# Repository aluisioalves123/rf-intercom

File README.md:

# RF Intercom

Interfone de apertar para falar, **sem fio**: as duas unidades conversam por rádio (nRF24L01+ com antena) e só precisam de uma tomada. Na prática é um walkie talkie de mesa, ligado na energia em vez de bateria, e por isso o nome interfone.

Projeto completo feito em casa: circuito, placa de circuito impresso fresada numa CNC caseira, firmware de áudio digital e caixa impressa em 3D.

**As duas unidades conversando** (com som):

https://github.com/user-attachments/assets/871d9580-77c3-4d14-9feb-cfa74ef9aef5

## Como funciona

1. Ao apertar o botão, a unidade toca um bipe curto e passa a transmitir.
2. O microfone de eletreto passa por um pré-amplificador com um transistor BC547 e chega na entrada analógica do Arduino.
3. O Arduino amostra a voz a 8 kHz, com 8 bits, junta 32 amostras em cada pacote e envia pelo nRF24 a 250 kbps.
4. A outra unidade guarda os pacotes numa fila circular e os toca no ritmo certo, por interrupção de timer, gerando o áudio por PWM.
5. O sinal passa pelo potenciômetro de volume e pelo amplificador PAM8403 até o alto-falante.

Ao soltar o botão, a unidade volta a escutar. O mesmo firmware roda nas duas unidades.

## Hardware

| Bloco | Componentes |
|---|---|
| MCU | Arduino Nano ou LGT8F328P (mesma pinagem) |
| Rádio | Módulo nRF24L01+ PA/LNA com antena SMA, desacoplado com 100 µF + 100 nF |
| Microfone | Cápsula de eletreto + pré-amplificador com BC547, alimentação filtrada por RC |
| Saída de áudio | PWM no D9, resistor de 33k, potenciômetro de 5k e módulo PAM8403 |
| Alto-falante | 8 Ω, 40 mm |
| Alimentação | 5 V pelo USB do Arduino; 3,3 V do próprio Arduino para o rádio |

O esquemático e a placa estão em [`hardware/`](hardware/) (KiCad).

## Placa

A placa tem 85 × 52 mm, face simples, com solda só no lado de baixo. Ela foi pensada desde o início para ser fresada em casa: ilhas grandes, trilhas de 1 mm, isolação de 0,5 mm, áreas livres nos cantos para as garras e dois fiduciais para alinhar a placa virada.

O **posicionamento e o roteamento** foram feitos por um plugin de KiCad que eu desenvolvi para posicionamento e roteamento automáticos. A fabricação usou os meus plugins para a fresa, que geram o G-code direto do KiCad, com voos de teste antes de cortar e medição da altura da placa:

- Plugin de posicionamento e roteamento para KiCad: [kicad-cnc-router](https://github.com/aluisioalves123/kicad-cnc-router)
- Plugins da fresa (exportação do KiCad e Candle): [fresa-pcb](https://github.com/aluisioalves123/fresa-pcb)

Os arquivos de fabricação estão em [`hardware/fabrication/`](hardware/fabrication/): gerbers, G-code das três fases (cobre de cima, furação, cobre de baixo) e o passo a passo de montagem com uma imagem por etapa.

Saindo da fresa, debaixo do pó de fenolite:

Placa fresada, vista contra a luz:

## Firmware

Em [`firmware/`](firmware/), para a Arduino IDE com a biblioteca [RF24](https://github.com/nRF24/RF24):

| Sketch | Para que serve |
|---|---|
| `intercom` | Firmware das duas unidades |
| `intercom_debug` | Igual ao `intercom`, mais um contador de pacotes por segundo no Monitor Serial (usado para diagnosticar o rádio) |
| `mic_test` | Mostra o sinal do microfone no Plotter Serial, para testar o pré-amplificador |

Pontos principais:

- **Áudio a 8 kHz:** a captura é cronometrada por `micros()`, e a reprodução usa uma interrupção do Timer2 a 8 kHz.
- **Fila circular de 256 amostras**, com índices de 8 bits que dão a volta sozinhos. A reprodução só começa com 96 amostras guardadas, para absorver a irregularidade do rádio.
- **PWM rápido de 8 bits no Timer1** para o áudio. Quando não está tocando, o pino fica solto, para não gerar chiado.
- **Remoção do nível DC do microfone** por média móvel, com ganho ajustável.
- **Rádio sem confirmação de recebimento:** em áudio ao vivo, reenviar um pacote atrasado é pior do que perdê-lo.
- **Funciona nos dois microcontroladores:** o Timer2 se ajusta ao clock (16 MHz no Nano, 32 MHz no LGT).

## Caixa

Em [`mechanical/`](mechanical/): modelada em OpenSCAD a partir das medidas reais da placa montada e impressa em PETG.

- A placa fica virada dentro da caixa, com o rádio, o botão e o amplificador voltados para a tampa.
- Saída retangular para o USB e rasgo para a antena, fechado por uma lingueta da tampa.
- Alto-falante preso por três presilhas de encaixe. Knob próprio para o potenciômetro.
- Tampa presa por parafusos M3 autoatarraxantes, deitados nas paredes compridas.

Os STLs prontos estão em [`mechanical/stl/`](mechanical/stl/), e o [`assembly.scad`](mechanical/assembly.scad) mostra a placa dentro da caixa.

As imagens do modelo são de uma versão anterior da caixa: grade do alto-falante com furos redondos e pinos compridos na tampa, que foram retirados. A versão atual usa rasgos na grade, como na unidade da esquerda na foto do topo.

## O que deu errado e como foi resolvido

**Mau contato na própria protoboard.** Um bloco falhava, mas o componente funcionava em outro lugar da protoboard, então o problema não era ele. Embaixo da protoboard havia protuberâncias no plástico. Abrindo, as barras metálicas estavam quase saindo dos encaixes. Recoloquei as barras e reforcei com fita isolante, e a partir daí o nRF24 passou a funcionar.

**PAM8403 oscilando.** A alimentação do amplificador era compartilhada com os outros módulos da montagem. Um fio dedicado, direto da alimentação do Arduino até o PAM8403, sem passar por outros componentes, resolveu.

**Ruído da alimentação USB.** Ligado no USB de um computador, aparece um ruído no áudio. Filtros RC em vários pontos do circuito (inclusive nas alimentações do microfone e do pré-amplificador) reduziram bastante, mas não eliminaram. Num carregador de tomada ou numa fonte de bancada, ele desaparece.

**Curto entre 5 V e GND na placa fresada.** A placa media 0,8 Ω entre 5 V e GND, e a primeira ligação queimou o diodo de proteção do USB do Nano. Para achar o curto, injetei 0,5 V com limite de corrente na rede de 5 V e medi a queda de tensão, em milivolts, em vários pontos da rede: o ponto com a menor leitura é o mais perto do curto. Foram duas causas: uma bolinha de solda encostando no plano de GND e "dentes" deixados por uma fresa gasta perto do capacitor C7. O Nano e o LGT voltaram a funcionar com um jumper no lugar do diodo queimado.

**Furos da tampa desalinhados.** A tampa é impressa de cabeça para baixo e virada na montagem, e virar espelha a frente com o fundo. O modelo não compensava isso, então os furos ficavam 2 mm fora e a lingueta da antena caía do lado errado. O arquivo de impressão passou a sair espelhado.

**Primeira camada do PETG.** Os furinhos redondos da grade do alto-falante soltavam da mesa na primeira camada. A grade virou rasgos compridos, e o furo do microfone virou uma estrela de três braços, num furo só.

**Potenciômetro queimado na montagem.** Soldar fios direto nas pernas do potenciômetro, feitas para ir espetadas numa placa, estragou o contato interno do cursor. O volume caía quase a zero.

## O que eu aprendi

**Validar em pequenos degraus.** A vontade de ver tudo funcionando é grande, e a tentação é montar tudo e testar só no final. Quando dá errado assim, fica difícil saber o que funcionou e o que não funcionou. O que salvou este projeto foi separar as partes: testar o nRF24 sozinho, depois o resto do circuito sozinho, e só então os dois juntos, até dar certo. O mesmo valeu para o áudio: o sistema de som foi testado sem nada do rádio, os microfones foram testados isoladamente, e assim por diante. Isso deixou claro o problema de cada parte, e juntando aos poucos deu para perceber como uma interferia na outra.

**Dois nRF24 muito próximos se atrapalham.** Com as unidades lado a lado e o amplificador do rádio em potência alta, a comunicação falha. Em potência baixa funciona perto e ainda alcança outros cômodos.

**O plano de GND faz muita diferença.** Na perfboard eu tinha muita dificuldade de conseguir um sinal de voz bom. Na placa de cobre fresada, com o plano de GND, a qualidade melhorou muito, mesmo com o ruído da alimentação USB.

**Capacitores de desacoplamento são essenciais**, tanto para a qualidade do sinal quanto para a estabilidade do circuito como um todo.

**Filtros RC no áudio.** Eu nunca tinha trabalhado com microfone. Aprender a filtrar a alimentação do eletreto e do pré-amplificador foi uma parte importante do projeto.

**Fresa e impressão 3D.** As duas eram novidade para mim, e boa parte do aprendizado veio delas: fabricar a placa em casa e desenhar a caixa a partir das medidas reais.

### Próximos passos

A melhoria mais imediata seria uma **bateria própria**. Além de tornar o interfone portátil, ela eliminaria de vez o ruído da alimentação USB.

## Estrutura do repositório

```
rf-intercom/
├── hardware/          projeto KiCad (esquemático, placa, biblioteca)
│   └── fabrication/   gerbers, G-code e passo a passo de montagem
├── firmware/          sketches do Arduino
├── mechanical/        caixa e knob em OpenSCAD, e os STLs
└── docs/              esquemático exportado e fotos
```

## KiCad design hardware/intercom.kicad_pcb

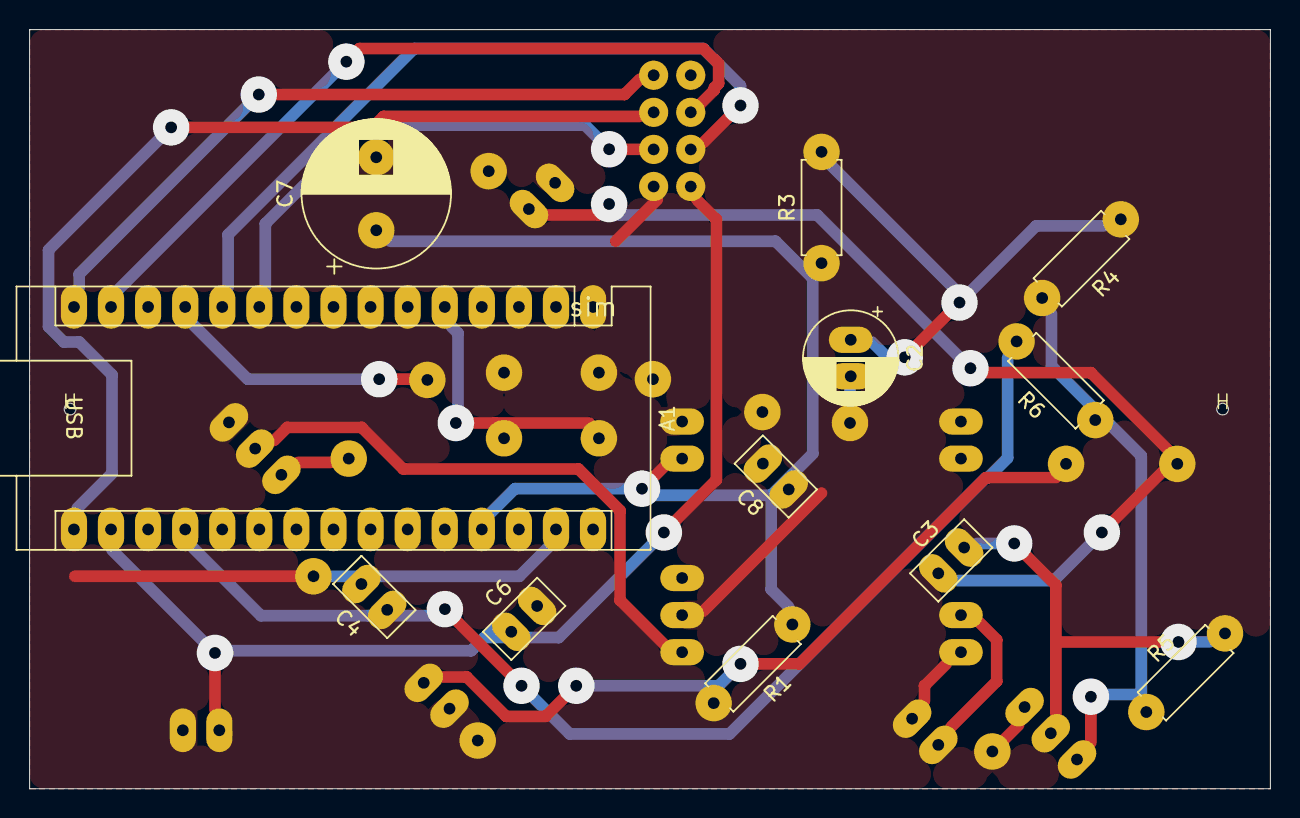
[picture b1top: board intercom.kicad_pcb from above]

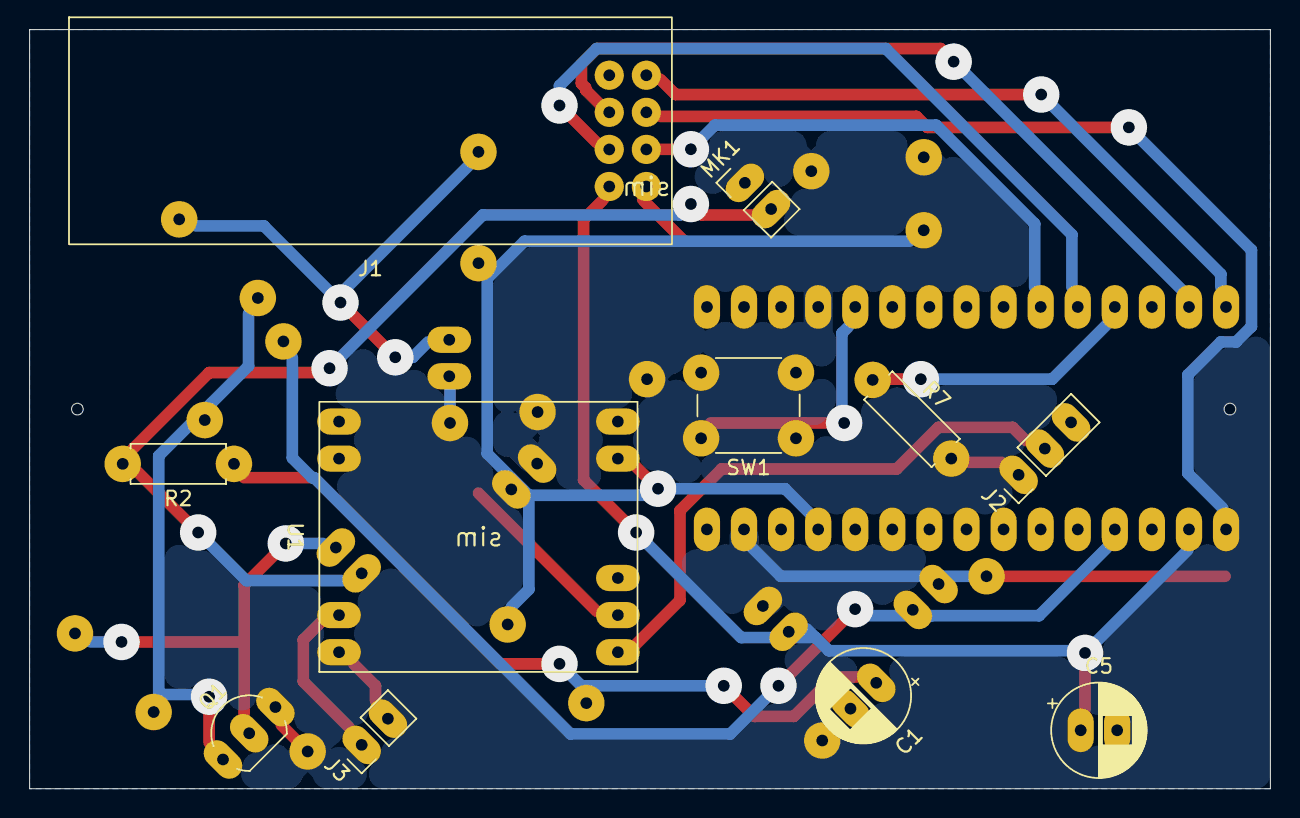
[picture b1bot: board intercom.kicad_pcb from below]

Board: 2 copper layers, 85.0 x 52.0 mm, 32 parts (11 on the bottom side), 20 nets.

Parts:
A1: Nano or LGT8F328P; Arduino_Nano
C1, C2, C5: 100uF; CP_Radial_D6.3mm_P2.50mm
C3: 100nF (104); C_Disc_D5.0mm_W2.5mm_P2.50mm
C4: 10nF (103); C_Disc_D5.0mm_W2.5mm_P2.50mm
C6, C8: 100nF; C_Disc_D5.0mm_W2.5mm_P2.50mm
C7: 1000uF; CP_Radial_D10.0mm_P5.00mm
H: Fiducial_Furo_0.8
H#2: Fiducial_Furo_0.8
J1: nRF24 PA+LNA; nRF24L01_PA_LNA_Module
J2: 5k pot (top, wiper, GND); PinHeader_1x03_P2.54mm_Vertical
J3: 8 ohm speaker; PinHeader_1x02_P2.54mm_Vertical
MK1: Electret; PinHeader_1x02_P2.54mm_Vertical
Q1: BC547; TO-92_Inline_Wide
R1: 1k; R_Axial_DIN0207_L6.3mm_D2.5mm_P7.62mm_Horizontal
R2, R4, R6: 2k2; R_Axial_DIN0207_L6.3mm_D2.5mm_P7.62mm_Horizontal
R3: 100; R_Axial_DIN0207_L6.3mm_D2.5mm_P7.62mm_Horizontal
R5: 1M; R_Axial_DIN0207_L6.3mm_D2.5mm_P7.62mm_Horizontal
R7: 33k; R_Axial_DIN0207_L6.3mm_D2.5mm_P7.62mm_Horizontal
SW1: Talk; SW_PUSH_6mm
U1: PAM8403; PAM8403_Module
VIAT1, VIAT2, VIAT3, VIAT4, VIAT5, VIAT6, VIAT7: via; via_termica

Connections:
+3V3: A1.17 (3V3), C5.1, C6.1, J1.2
+5V: A1.27 (+5V), C7.1, C8.1, R1.1, R3.1, U1.4
/AMP_IN: J2.2, U1.1
/AUDIO_PWM: A1.12 (D9), R7.1
/MIC_BIAS: C3.1, MK1.2 (+), R2.2
/MIC_OUT: A1.19 (A0), C4.1, R6.2
/MIC_SUPPLY: C1.1, R1.2, R2.1
/POT_TOP: J2.1, R7.2
/PREAMP_IN: C3.2, Q1.2 (B), R5.2
/PREAMP_OUT: Q1.1 (C), R4.2, R5.1, R6.1
/PREAMP_SUPPLY: C2.1, R3.2, R4.1
/PTT_BUTTON: A1.5 (D2), SW1.1
/RADIO_CE: A1.10 (D7), J1.3
/RADIO_CSN: A1.11 (D8), J1.4
/SPEAKER+: J3.1, U1.7
/SPEAKER-: J3.2, U1.6
/SPI_MISO: A1.15 (D12), J1.7
/SPI_MOSI: A1.14 (D11), J1.6
/SPI_SCK: A1.16 (D13), J1.5
GND: A1.4 (GND), A1.29 (GND), C1.2, C2.2, C4.2, C5.2, C6.2, C7.2, C8.2, J1.1, J2.3, MK1.1 (-), Q1.3 (E), SW1.2, U1.2, U1.5, VIAT1.1, VIAT2.1, VIAT3.1, VIAT4.1, VIAT5.1, VIAT6.1, VIAT7.1

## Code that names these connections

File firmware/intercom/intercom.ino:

// RF push-to-talk intercom (nRF24L01+PA+LNA)
// The same sketch runs on both units.
// Board: select "Arduino Nano" or "LGT8F328" in the Arduino IDE.
// Library: RF24 (TMRh20)
//
// Wiring (intercom.kicad_pcb):
//   D2   push-to-talk button (to GND)
//   D7   nRF24 CE
//   D8   nRF24 CSN
//   D9   audio out (PWM) -> R7 -> volume pot -> PAM8403
//   A0   microphone (BC547 preamp output)
//   D11  MOSI, D12 MISO, D13 SCK (nRF24 SPI)

#include <SPI.h>
#include <RF24.h>

// ---------- pins ----------
const byte PTT_BUTTON_PIN = 2;
const byte RADIO_CE_PIN   = 7;
const byte RADIO_CSN_PIN  = 8;
const byte AUDIO_OUT_PIN  = 9;      // OC1A
const byte MIC_PIN        = A0;

// ---------- tuning ----------
const unsigned long SAMPLE_PERIOD_US = 125;   // 8000 samples per second
const byte RADIO_CHANNEL = 100;               // above the Wi-Fi channels
const int  MIC_GAIN = 4;                      // talker volume: 2 (quiet) to 8 (loud)
const byte PLAYBACK_START_THRESHOLD = 96;     // samples buffered before playback starts
const unsigned long RECEIVE_TIMEOUT_MS = 150; // silence that ends a transmission
const byte PACKET_SIZE = 32;                  // nRF24 maximum payload

const byte RADIO_ADDRESS[6] = "INTF1";

RF24 radio(RADIO_CE_PIN, RADIO_CSN_PIN);

// ---------- playback ring buffer (256 bytes, byte indices wrap around on their own) ----------
volatile byte playbackBuffer[256];
volatile byte playbackReadIndex = 0;
volatile byte playbackWriteIndex = 0;
volatile byte lastPlayedSample = 128;

// ---------- state ----------
bool isTalking = false;
bool isPlaying = false;
unsigned long nextSampleTimeUs = 0;
unsigned long lastPacketReceivedMs = 0;
long micDcLevelTimes64 = 512L << 6;   // slow average of the mic signal (x64), used to remove the DC offset
byte outgoingPacket[PACKET_SIZE];
byte outgoingPacketLength = 0;

bool lastRawButtonState = false;
unsigned long buttonChangedAtMs = 0;
const unsigned long BUTTON_DEBOUNCE_MS = 20;

// ================= audio output =================

void enableAudioPwm() {
  pinMode(AUDIO_OUT_PIN, OUTPUT);
  OCR1A = 128;
  TCCR1A = _BV(COM1A1) | _BV(WGM10);    // 8-bit fast PWM on D9
  TCCR1B = _BV(WGM12) | _BV(CS10);      // no prescaler
}

void releaseAudioPin() {
  TCCR1A &= ~_BV(COM1A1);               // disconnect PWM from the pin
  digitalWrite(AUDIO_OUT_PIN, LOW);
  pinMode(AUDIO_OUT_PIN, INPUT);        // floating pin: no idle hiss
}

void setupPlaybackTimer() {             // Timer2 interrupt at 8 kHz
  TCCR2A = _BV(WGM21);                  // CTC mode
#if (F_CPU / 8 / 8000) <= 256
  TCCR2B = _BV(CS21);                   // prescaler 8
  OCR2A = (F_CPU / 8 / 8000) - 1;
#else
  TCCR2B = _BV(CS21) | _BV(CS20);       // prescaler 32 (LGT at 32 MHz)
  OCR2A = (F_CPU / 32 / 8000) - 1;
#endif
  TIMSK2 = 0;                           // starts disabled
}

ISR(TIMER2_COMPA_vect) {
  if (playbackReadIndex != playbackWriteIndex) {
    lastPlayedSample = playbackBuffer[playbackReadIndex];
    playbackReadIndex++;
  }
  OCR1A = lastPlayedSample;
}

void startPlayback() {
  enableAudioPwm();
  TCNT2 = 0;
  TIMSK2 = _BV(OCIE2A);
  isPlaying = true;
}

void stopPlayback() {
  TIMSK2 = 0;
  releaseAudioPin();
  playbackReadIndex = playbackWriteIndex;
  lastPlayedSample = 128;
  isPlaying = false;
}

// short ~880 Hz beep when the button is pressed
void playTalkBeep() {
  enableAudioPwm();
  unsigned long startMs = millis();
  bool high = false;
  while (millis() - startMs < 120) {
    high = !high;
    OCR1A = high ? 60 : 0;
    delayMicroseconds(568);
  }
  releaseAudioPin();
}

// ================= modes =================

void enterTalkMode() {
  stopPlayback();
  radio.stopListening();
  outgoingPacketLength = 0;
}

void enterListenMode() {
  radio.txStandBy();
  radio.startListening();
}

// ================= microphone =================

byte readMicSample() {
  int raw = analogRead(MIC_PIN);                       // 0 to 1023
  micDcLevelTimes64 += raw - (micDcLevelTimes64 >> 6); // slow running average
  int sample = raw - (int)(micDcLevelTimes64 >> 6);    // keep only the varying part
  sample = (sample * MIC_GAIN) / 4 + 128;
  if (sample < 0) sample = 0;
  if (sample > 255) sample = 255;
  return (byte)sample;
}

// ================= setup and loop =================

void setup() {
  Serial.begin(115200);
  pinMode(PTT_BUTTON_PIN, INPUT_PULLUP);
  pinMode(10, OUTPUT);                  // D10 as output keeps the SPI in master mode
  releaseAudioPin();

#if defined(__LGT8F__)
  analogReadResolution(10);
#else
  ADCSRA = (ADCSRA & 0xF8) | 0x05;      // faster ADC (prescaler 32)
#endif

  if (!radio.begin()) {
    Serial.println(F("nRF24 not responding, check the wiring"));
    while (true) {}
  }
  radio.setChannel(RADIO_CHANNEL);
  radio.setDataRate(RF24_250KBPS);
  radio.setPALevel(RF24_PA_LOW);        // LOW is plenty inside a house (HIGH or MAX for longer range)
  radio.setAutoAck(false);
  radio.setCRCLength(RF24_CRC_16);
  radio.setPayloadSize(PACKET_SIZE);
  radio.openWritingPipe(RADIO_ADDRESS);
  radio.openReadingPipe(1, RADIO_ADDRESS);
  radio.startListening();

  setupPlaybackTimer();
  Serial.println(F("intercom ready"));
}

void loop() {
  // ---- push-to-talk button with debounce ----
  bool rawButtonPressed = (digitalRead(PTT_BUTTON_PIN) == LOW);
  if (rawButtonPressed != lastRawButtonState) {
    lastRawButtonState = rawButtonPressed;
    buttonChangedAtMs = millis();
  }
  bool buttonPressed = (millis() - buttonChangedAtMs > BUTTON_DEBOUNCE_MS) ? rawButtonPressed : isTalking;

  if (buttonPressed && !isTalking) {
    enterTalkMode();
    playTalkBeep();
    isTalking = true;
    nextSampleTimeUs = micros();
  } else if (!buttonPressed && isTalking) {
    isTalking = false;
    enterListenMode();
  }

  // ---- talking: sample the mic and send 32-byte packets ----
  if (isTalking) {
    if ((long)(micros() - nextSampleTimeUs) >= 0) {
      nextSampleTimeUs += SAMPLE_PERIOD_US;
      outgoingPacket[outgoingPacketLength++] = readMicSample();
      if (outgoingPacketLength == PACKET_SIZE) {
        radio.writeFast(outgoingPacket, PACKET_SIZE);
        outgoingPacketLength = 0;
      }
    }
    return;
  }

  // ---- listening: buffer what arrives and play it ----
  while (radio.available()) {
    byte freeSpace = 255 - (byte)(playbackWriteIndex - playbackReadIndex);
    if (freeSpace >= PACKET_SIZE) {
      byte incomingPacket[PACKET_SIZE];
      radio.read(incomingPacket, PACKET_SIZE);
      for (byte i = 0; i < PACKET_SIZE; i++) {
        playbackBuffer[playbackWriteIndex] = incomingPacket[i];
        playbackWriteIndex++;
      }
    } else {
      break;                            // buffer full, read it on the next pass
    }
    lastPacketReceivedMs = millis();
  }

  byte bufferedSamples = (byte)(playbackWriteIndex - playbackReadIndex);
  if (!isPlaying && bufferedSamples >= PLAYBACK_START_THRESHOLD) {
    startPlayback();
  }
  if (isPlaying && bufferedSamples == 0 && millis() - lastPacketReceivedMs > RECEIVE_TIMEOUT_MS) {
    stopPlayback();
  }
}
